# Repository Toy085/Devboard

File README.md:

# Info about the devboard

This devboard is bulit using the RP2040 microcontroller. It features a USB-C connector for power and data, and 16 Mbit of external flash storage.

### Images of the devboard:

### BOM:
Available in .csv format: [bom.csv](https://github.com/Toy085/Devboard/blob/main/bom.csv)

|  Item | Qty | Link |
| ------| --- | ------|
| 0.1uF Capacitor | 11 | https://jlcpcb.com/partdetail/1877-CL05B104KO5NNNC/C1525 |
| 1uF Capacitor | 2 | https://jlcpcb.com/partdetail/53938-CL05A105KA5NQNC/C52923 |
| 10uF Capacitor | 2 | https://jlcpcb.com/partdetail/20411-CL10A106KP8NNNC/C19702 |
| 33pF Capacitor | 2 | https://jlcpcb.com/partdetail/1914-0402CG330J500NT/C1562 |
| Male USB C Header | 1 | https://jlcpcb.com/partdetail/Korean_HropartsElec-TYPE_C_31_M12/C165948 |
| 1x20 pin header | 2 | https://jlcpcb.com/partdetail/51993-2_54_1_20PStraightpin/C50981 |
| 1x3 pin header | 1 | https://jlcpcb.com/partdetail/50265-2_54_13PPin/C49257 |
| RP2040 | 1 | https://jlcpcb.com/partdetail/RaspberryPi-RP2040/C2040 |
| Button | 1 | https://jlcpcb.com/partdetail/XUNPU-TS_1088AR02016/C720477 |
| 5.1K Resistor | 2 | https://jlcpcb.com/partdetail/26648-0402WGF5101TCE/C25905 |
| 1K Resistor | 2 | https://jlcpcb.com/partdetail/12256-0402WGF1001TCE/C11702 |
| 27Ω Resistor | 2 | https://jlcpcb.com/partdetail/25843-0402WGF270JTCE/C25100 |
| 10K Resistor | 1 | https://jlcpcb.com/partdetail/26487-0402WGF1002TCE/C25744 |
| 12MHz Crystal Oscillator | 1 | https://jlcpcb.com/partdetail/NDK-NX3225GA_12MHZ_STD_CRG2/C481407 |
| Transistor | 1 | https://jlcpcb.com/partdetail/2489-2SA812_RANGE_300_400/C2132 |
| Flash storage | 1 | https://jlcpcb.com/partdetail/WinbondElec-W25Q16JVUXIQ/C2843335 |

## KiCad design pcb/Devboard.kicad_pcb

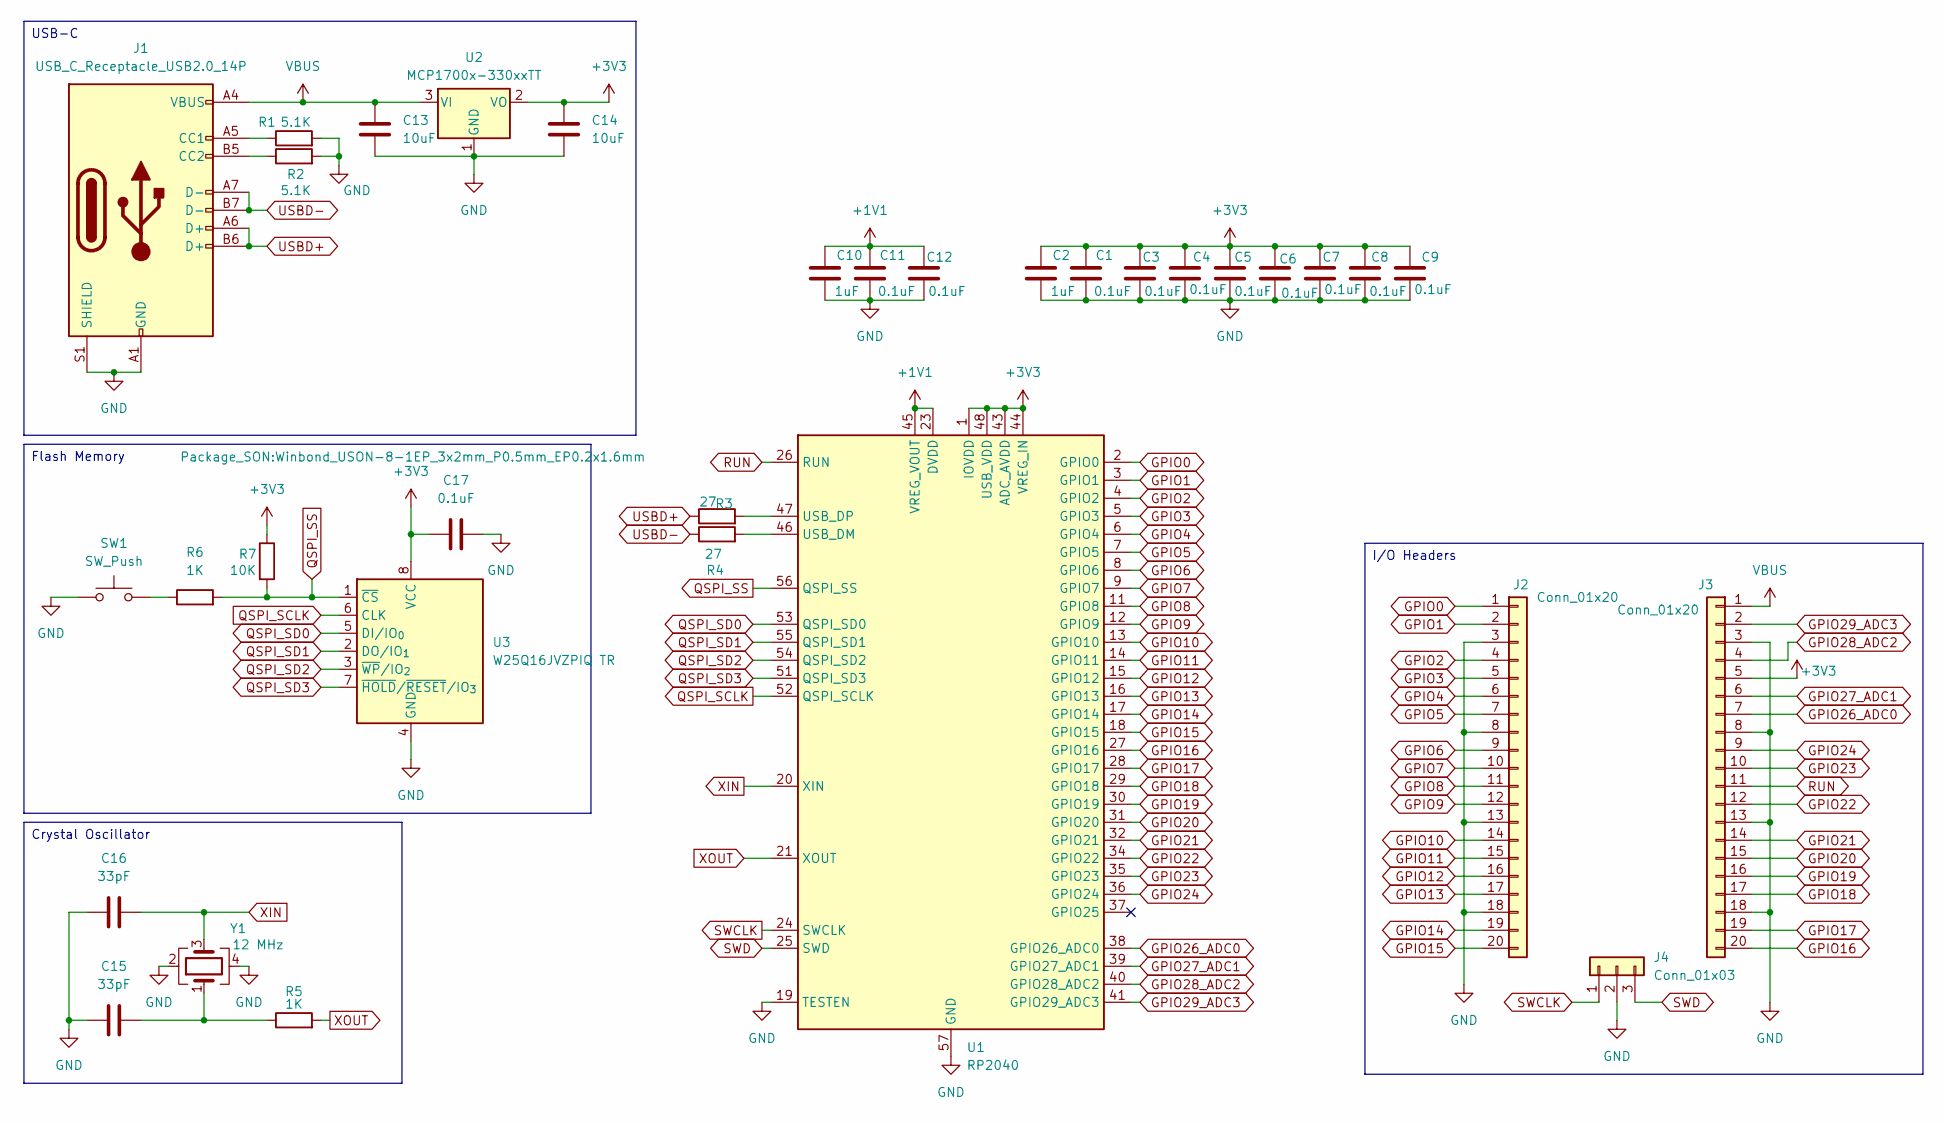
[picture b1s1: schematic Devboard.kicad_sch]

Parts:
C1, C3, C4, C5, C6, C7, C8, C9, C11, C12, C17: 0.1uF; C_0402_1005Metric
C2, C10: 1uF; C_0402_1005Metric
C13, C14: 10uF; C_0603_1608Metric
C15, C16: 33pF; C_0402_1005Metric
J1: USB_C_Receptacle_USB2.0_14P; USB_C_Receptacle_HRO_TYPE-C-31-M-12
J2, J3: Conn_01x20; PinHeader_1x20_P2.54mm_Vertical
J4: Conn_01x03; PinHeader_1x03_P2.54mm_Vertical
R1, R2: 5.1K; C_0402_1005Metric
R3, R4: 27; C_0402_1005Metric
R5, R6: 1K; C_0402_1005Metric
R7: 10K; C_0402_1005Metric
SW1: SW_Push; SW_Push_SPST_NO_Alps_SKRK
U1: RP2040; QFN-56-1EP_7x7mm_P0.4mm_EP3.2x3.2mm
U2: MCP1700x-330xxTT; SOT-23
U3: W25Q16JVZPIQ TR; Winbond_USON-8-1EP_3x2mm_P0.5mm_EP0.2x1.6mm
Y1: 12 MHz; Crystal_SMD_3225-4Pin_3.2x2.5mm

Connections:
+1V1: C10.1, C11.1, C12.1, U1.23 (DVDD), U1.45 (VREG_VOUT), U1.50 (DVDD)
+3V3: C1.1, C2.1, C3.1, C4.1, C5.1, C6.1, C7.1, C8.1, C9.1, C14.1, C17.1, J3.5, R7.1, U1.1 (IOVDD), U1.10 (IOVDD), U1.22 (IOVDD), U1.33 (IOVDD), U1.42 (IOVDD), U1.43 (ADC_AVDD), U1.44 (VREG_IN), U1.48 (USB_VDD), U1.49 (IOVDD), U2.2 (VO), U3.8 (VCC)
GND: C1.2, C2.2, C3.2, C4.2, C5.2, C6.2, C7.2, C8.2, C9.2, C10.2, C11.2, C12.2, C13.2, C14.2, C15.1, C16.1, C17.2, J1.A1 (GND), J1.A12 (GND), J1.B1 (GND), J1.B12 (GND), J1.S1 (SHIELD), J2.3, J2.8, J2.13, J2.18, J3.3, J3.8, J3.13, J3.18, J4.2, R1.2, R2.2, SW1.1, U1.19 (TESTEN), U1.57 (GND), U2.1 (GND), U3.4 (GND), Y1.2, Y1.4
GPIO0: J2.1, U1.2 (GPIO0)
GPIO1: J2.2, U1.3 (GPIO1)
GPIO2: J2.4, U1.4 (GPIO2)
GPIO3: J2.5, U1.5 (GPIO3)
GPIO4: J2.6, U1.6 (GPIO4)
GPIO5: J2.7, U1.7 (GPIO5)
GPIO6: J2.9, U1.8 (GPIO6)
GPIO7: J2.10, U1.9 (GPIO7)
GPIO8: J2.11, U1.11 (GPIO8)
GPIO9: J2.12, U1.12 (GPIO9)
GPIO10: J2.14, U1.13 (GPIO10)
GPIO11: J2.15, U1.14 (GPIO11)
GPIO12: J2.16, U1.15 (GPIO12)
GPIO13: J2.17, U1.16 (GPIO13)
GPIO14: J2.19, U1.17 (GPIO14)
GPIO15: J2.20, U1.18 (GPIO15)
GPIO16: J3.20, U1.27 (GPIO16)
GPIO17: J3.19, U1.28 (GPIO17)
GPIO18: J3.17, U1.29 (GPIO18)
GPIO19: J3.16, U1.30 (GPIO19)
GPIO20: J3.15, U1.31 (GPIO20)
GPIO21: J3.14, U1.32 (GPIO21)
GPIO22: J3.12, U1.34 (GPIO22)
GPIO23: J3.10, U1.35 (GPIO23)
GPIO24: J3.9, U1.36 (GPIO24)
GPIO26_ADC0: J3.7, U1.38 (GPIO26_ADC0)
GPIO27_ADC1: J3.6, U1.39 (GPIO27_ADC1)
GPIO28_ADC2: J3.4, U1.40 (GPIO28_ADC2)
GPIO29_ADC3: J3.2, U1.41 (GPIO29_ADC3)
unnamed: C15.2, R5.1, Y1.1
unnamed: J1.A5 (CC1), R1.1
unnamed: J1.B5 (CC2), R2.1
unnamed: R6.1, SW1.2
unnamed: R4.2, U1.46 (USB_DM)
unnamed: R3.2, U1.47 (USB_DP)
QSPI_SCLK: U1.52 (QSPI_SCLK), U3.6 (CLK)
QSPI_SD0: U1.53 (QSPI_SD0), U3.5 (DI/IO_{0})
QSPI_SD1: U1.55 (QSPI_SD1), U3.2 (DO/IO_{1})
QSPI_SD2: U1.54 (QSPI_SD2), U3.3 (~WP/IO_{2})
QSPI_SD3: U1.51 (QSPI_SD3), U3.7 (~HOLD/~RESET/IO_{3})
QSPI_SS: R6.2, R7.2, U1.56 (QSPI_SS), U3.1 (~CS)
RUN: J3.11, U1.26 (RUN)
SWCLK: J4.1, U1.24 (SWCLK)
SWD: J4.3, U1.25 (SWD)
USBD+: J1.A6 (D+), J1.B6 (D+), R3.1
USBD-: J1.A7 (D-), J1.B7 (D-), R4.1
VBUS: C13.1, J1.A4 (VBUS), J1.A9 (VBUS), J1.B4 (VBUS), J1.B9 (VBUS), J3.1, U2.3 (VI)
XIN: C16.2, U1.20 (XIN), Y1.3
XOUT: R5.2, U1.21 (XOUT)

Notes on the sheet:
Flash Memory
I/O Headers
Crystal Oscillator
USB-C

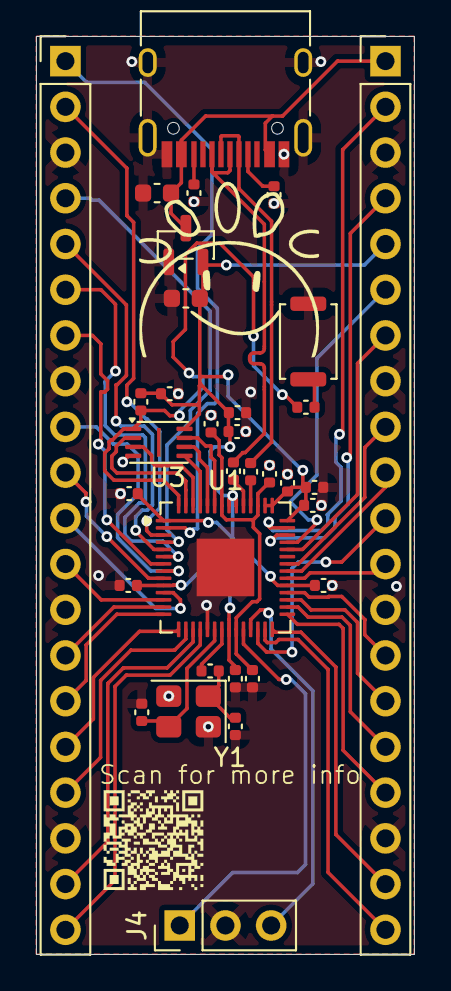
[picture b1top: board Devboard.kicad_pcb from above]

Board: 2 copper layers, 21.0 x 51.0 mm, 33 parts (0 on the bottom side), 52 nets.

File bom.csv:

Designator,Footprint,Quantity,Value,LCSC Part #
"C1, C11, C12, C17, C3, C4, C5, C6, C7, C8, C9",0402,11,0.1uF,
"C10, C2",0402,2,1uF,
"C13, C14",0603,2,10uF,
"C15, C16",0402,2,33pF,
J1,USB_C_Receptacle_HRO_TYPE-C-31-M-12,1,USB_C_Receptacle_USB2.0_14P,
"J2, J3",PinHeader_1x20_P2.54mm_Vertical,2,Conn_01x20,
J4,PinHeader_1x03_P2.54mm_Vertical,1,Conn_01x03,
"R1, R2",0402,2,5.1K,
"R3, R4",0402,2,27,
"R5, R6",0402,2,1K,
R7,0402,1,10K,
SW1,SW_Push_SPST_NO_Alps_SKRK,1,SW_Push,
U1,QFN-56-1EP_7x7mm_P0.4mm_EP3.2x3.2mm,1,RP2040,
U2,SOT-23,1,MCP1700x-330xxTT,
U3,Winbond_USON-8-1EP_3x2mm_P0.5mm_EP0.2x1.6mm,1,W25Q16JVZPIQ TR,
Y1,Crystal_SMD_3225-4Pin_3.2x2.5mm,1,12 MHz,

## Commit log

2026-02-07 Add initial README with project title
2026-02-07 Add BOM section to README
2026-02-07 Change BOM header format in README
2026-02-10 Add images of the devboard to README
    Added images of the devboard to the README.
2026-02-10 Update README structure and add BOM link
    Reorganized sections to place images before BOM and added link to BOM in CSV format.
2026-02-10 Add BOM table to README
    Added a BOM table with component details and links.
2026-02-10 Update README with new components and links
    Added additional components including buttons and resistors with their respective links.
2026-02-10 Add RP2040 microcontroller details to README
    Added details about the RP2040 microcontroller and its features.
